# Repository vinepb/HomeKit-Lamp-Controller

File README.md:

# Lamp Controller with Apple HomeKit

## Overview

This project is a smart lamp controller designed for a 3V3 3D printed lamp. It utilizes an ESP32 microcontroller and integrates seamlessly with Apple's HomeKit ecosystem. The project consists of both software and hardware components, making it a complete solution for controlling the lamp remotely.

## Software

The software component of this project is based on the following technologies:

- [esp-idf](https://github.com/espressif/esp-idf): Espressif's IoT Development Framework.
- [esp-homekit-sdk](https://github.com/espressif/esp-homekit-sdk): A library for building HomeKit accessories for Espressif chips.

### Installation

Follow the installation instructions for [esp-idf](https://github.com/espressif/esp-idf), then clone [esp-homekit-sdk](https://github.com/espressif/esp-homekit-sdk). Then clone this repository:
```shell
git clone https://github.com/vinepb/HomeKit-Lamp-Controller.git
```
Then set the device's serial port and flash:
```shell
$ cd /path/to/lightbulb
$ export ESPPORT=/dev/tty.SLAB_USBtoUART # Set your board's serial port here
$ idf.py set-target esp32
$ idf.py flash monitor
```

As the device boots up, you will see two QR codes, a small one for HomeKit and a larger one for Wi-Fi provisioning. Please use any of the [Espressif Provisioning Apps](https://docs.espressif.com/projects/esp-idf/en/latest/esp32/api-reference/provisioning/provisioning.html#provisioning-tools) for Wi-Fi provisioning.

> Note: For the Open source HomeKit SDK, the HomeKit QR code cannot be used for provisioning from the Home app. It can be used only for pairing, after the Wi-Fi provisioning is done. For provisioning from Home app, you will need the MFi variant of the SDK.

> Note: If you want to use hard-coded credentials instead of Provisioning, please set the ssid and passphrase by navigating to `idf.py menuconfig -> App Wi-Fi -> Source of Wi-Fi Credentials -> Use Hardcoded`

After the device connects to your Home Wi-Fi network it can be added in the Home app

### Add acccessory in the Home app

Open the Home app on your iPhone/iPad and follow these steps

- Tap on "Add Accessory" and scan the small QR code mentioned above.
- If QR code is not visible correctly, you may use the link printed on the serial terminal or follow these steps:
    - Choose the "I Don't Have a Code or Cannot Scan" option.
    - Tap on "Esp-Light-xxxxxx" in the list of Nearby Accessories.
    - Select the "Add Anyway" option for the "Uncertified Accessory" prompt.
    - Enter 11122333 as the Setup code.
- You should eventually see the "Esp-Light-xxxxxx added" message.
- Give a custom name, assign to a room, create scenes as required and you are done.

## Hardware

The hardware component of ths project was designed using [KiCad](https://www.kicad.org) and includes a schematic and a PCB layout.

### PCB Layout

### List of Materials

| Component           | Quantity | Footprint                                        |
|---------------------|----------|--------------------------------------------------|
| Resistor 10k Ohm    | 1        | Resistor_THT:R_Axial_DIN0207_L6.3mm_D2.5mm_P10.16mm_Horizontal |
| Resistor 300 Ohm    | 3        | Resistor_THT:R_Axial_DIN0207_L6.3mm_D2.5mm_P10.16mm_Horizontal |
| Transistor 2N3906   | 1        | Package_TO_SOT_THT:TO-92_Inline                |
| Capacitor 10uF      | 3        | Capacitor_THT:C_Radial_D5.0mm_H11.0mm_P2.00mm |
| Regulator LM1117T 3V3 | 1      | Package_TO_SOT_THT:TO-220-3_Horizontal_TabDown |
| Regulator LM1117T 5V | 1       | Package_TO_SOT_THT:TO-220-3_Horizontal_TabDown |
| ESP32-WROOM-32      | 1        | DEVKIT V1                                        |
| Jack P4 Female      | 1        | Connector_BarrelJack:BarrelJack_Horizontal_3pin |
| 15x Pin Socket       | 2        | 2.54mm vertical                                  |
| Lamp Connector      | 1        | Connector_AMASS_XT30U-F_1x02_P5.0mm_Vertical  |
| 1m Red AWG 20 Cable   | 1        | -                                                |
| 1m Black AWG 20 Cable | 1        | -                                                |
| 9VDC P4 Power Supply  | 1        | -                                                |

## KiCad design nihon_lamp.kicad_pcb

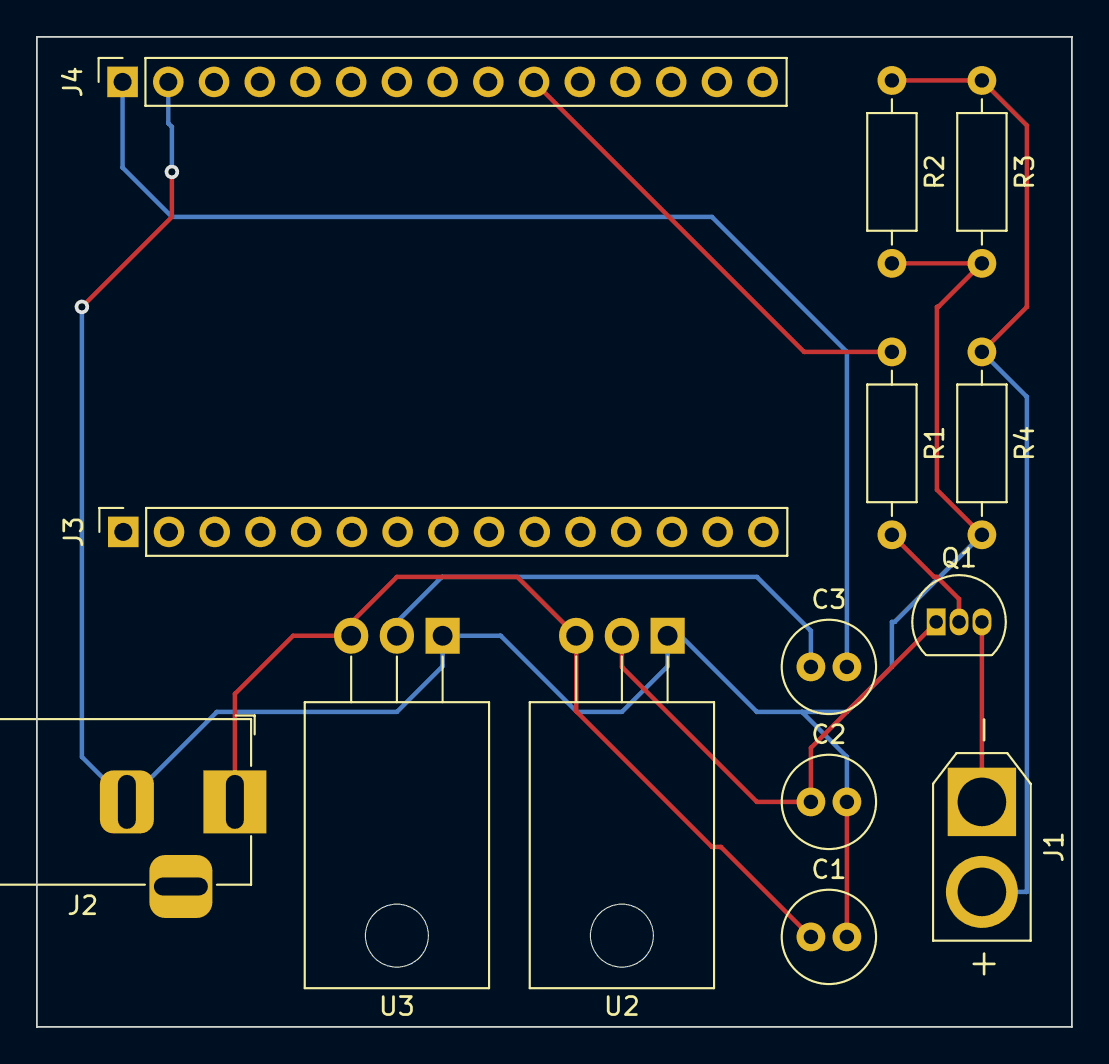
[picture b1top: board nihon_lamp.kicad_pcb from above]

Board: 2 copper layers, 57.5 x 55.0 mm, 14 parts (0 on the bottom side), 9 nets.

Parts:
C1, C2, C3: C; C_Radial_D5.0mm_H11.0mm_P2.00mm
J1: Lamp LED; AMASS_XT30U-F_1x02_P5.0mm_Vertical
J2: Barrel_Jack_MountingPin; BarrelJack_Horizontal
J3, J4: Conn_01x15_Pin; PinSocket_1x15_P2.54mm_Vertical
Q1: 2N3906; TO-92_Inline
R1: 10k; R_Axial_DIN0207_L6.3mm_D2.5mm_P10.16mm_Horizontal
R2, R3, R4: 300; R_Axial_DIN0207_L6.3mm_D2.5mm_P10.16mm_Horizontal
U2: LM1117T-3.3; TO-220-3_Horizontal_TabDown
U3: LM1117T-5.0; TO-220-3_Horizontal_TabDown

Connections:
+3V3: C2.1, Q1.1 (E), U2.2 (VO)
+5V: C3.1, U3.2 (VO)
+9V: C1.1, J2.1, U2.3 (VI), U3.3 (VI)
GND: C1.2, C2.2, J2.2, J4.2, R2.2, R3.2, R4.2, U2.1 (GND), U3.1 (GND)
unnamed: J1.1, Q1.3 (C)
unnamed: J1.2, R2.1, R3.1, R4.1
unnamed: C3.2, J4.1
unnamed: J4.10, R1.1
unnamed: Q1.2 (B), R1.2

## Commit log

2023-09-18 Add .gitignore
2023-09-18 Upload project
2023-10-06 add case 3d model
